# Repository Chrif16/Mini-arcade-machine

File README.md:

# Mini-arcade-machine
a small nes emulation console in the shape of an arcade machine. containing an esp32 s3 and a 2.8 inch tft screen.
this is a part of hackclub's half life event.

# Wiring
the micro controller used is an esp32 s3  because it has more computing power, the display is a standart 2.8 inch display, the controller is a joy stick plus 4 buttons for A,B,START and SELECT.i also used an audio amplifier and hooked it up to an 8ohm speaker. and also a micro sd card reader to read your game roms. 

# pcb
i put all the buttons and controls on the same pcb so that the wiring and mounting is a little bit easier

# 3D model
it has screw holes for mounting everything that has monting holes and the rest have stands that fix the part in place

# firmware
i used the anemoia esp32 nes emulator firmware and reconfigured it to work with my wiring and joystick support
thank you to the anemoia team for making my life easier and making this project possible.
# How to build
for screws and such it is recommended you find them localy for cheap. First, you should screw in place the components with screw holes, and then flash you esp32 s3, and after that youshould slide the speaker in place and plug in place the esp32 and the pam8043 amplifier. and finally solder wire between everything and close the lid and you've got yourself your very own arcade machine
# How to flash
Download and install the Arduino IDE.
In File → Preferences → Additional boards manager URLs , add:
https://espressif.github.io/arduino-esp32/package_esp32_index.json
Download the ESP32 board support v3.2.1 through Tools → Board → Boards Manager .
Important:Make sure to download version 3.2.1, as different board versions may have worse performance.
Navigate to your Arduino Libraries folder: (Default location): Documents/Arduino/libraries/TFT_eSPI
Copy your desired User_Setup.h file in the /User_Setups folder from this repository into TFT_eSPI/ and overwrite the file. Optionally, edit the #define pins as desired.
Download the SdFat and TFT_eSPI libraries from Tools → Manage Libraries .
Locate your ESP32 Arduino platform directory. This is typically at:
\Users\{username}\AppData\Local\Arduino15\packages\esp32\hardware\esp32\{version}\
Copy the platform.txt file from this repository and paste into that folder. This file defines additional compiler flags and optimizations used by Anemoia-ESP32.
Connect your ESP32 via USB.
In the Arduino IDE, go to Tools → Board and select your ESP32 s3 board .
Click Upload or press Ctrl+U to build and flash the emulator.
# BOM
|number of parts|part                      |link                                                                                                                                                                                                                                                                                                                                                                                                                                                                                                                                                                                                                                                                                                                                                                                                                                                                                                                                       |price |
|---------------|--------------------------|-------------------------------------------------------------------------------------------------------------------------------------------------------------------------------------------------------------------------------------------------------------------------------------------------------------------------------------------------------------------------------------------------------------------------------------------------------------------------------------------------------------------------------------------------------------------------------------------------------------------------------------------------------------------------------------------------------------------------------------------------------------------------------------------------------------------------------------------------------------------------------------------------------------------------------------------|------|
|1              |esp32 s3                  |https://ar.aliexpress.com/item/1005012593038007.html?spm=a2g0o.productlist.main.3.56fbd68dsFV1H7&algo_pvid=a583c642-2f95-4179-8c1e-22964e750e76&algo_exp_id=a583c642-2f95-4179-8c1e-22964e750e76-51&pdp_ext_f=%7B%22order%22%3A%2220%22%2C%22eval%22%3A%221%22%2C%22fromPage%22%3A%22search%22%7D&pdp_npi=6%40dis%21USD%213.30%212.04%21%21%213.30%212.04%21%40212a6e3217932889916021693e2399%2112000059750848637%21sea%21TN%210%21ABX%211%210%21n_tag%3A-29910%3Bd%3Aa568ec5c%3Bm03_new_user%3A-29895%3BpisId%3A5000000219357547&curPageLogUid=UTveZqjZShm2&utparam-url=scene%3Asearch%7Cquery_from%3A%7Cx_object_id%3A1005012593038007%7C_p_origin_prod%3A                                                                                                                                                                                                                                                                               |$3.3  |
|1              |joystick                  |https://ar.aliexpress.com/item/1005007846718456.html?spm=a2g0o.detail.pcDetailBottomMoreOtherSeller.2.21f2pCFkpCFkvH&gps-id=pcDetailBottomMoreOtherSeller&scm=1007.40050.354490.0&scm_id=1007.40050.354490.0&scm-url=1007.40050.354490.0&pvid=c3bb454c-9df1-4c85-98ab-45f0fbe84c14&_t=gps-id%3ApcDetailBottomMoreOtherSeller%2Cscm-url%3A1007.40050.354490.0%2Cpvid%3Ac3bb454c-9df1-4c85-98ab-45f0fbe84c14%2Ctpp_buckets%3A668%232846%238112%231997&pdp_ext_f=%7B%22order%22%3A%22173%22%2C%22eval%22%3A%221%22%2C%22sceneId%22%3A%2230050%22%2C%22fromPage%22%3A%22recommend%22%7D&pdp_npi=6%40dis%21USD%215.16%214.12%21%21%2134.22%2127.35%21%400b15841617932898666012194e106e%2112000042509532021%21rec%21TN%21%21ABX%211%210%21n_tag%3A-29910%3Bd%3Aa568ec5c%3Bm03_new_user%3A-29895%3BpisId%3A5000000219357547&utparam-url=scene%3ApcDetailBottomMoreOtherSeller%7Cquery_from%3A%7Cx_object_id%3A1005007846718456%7C_p_origin_prod%3A|$5.17 |
|4              |tactile switch            |https://ar.aliexpress.com/item/1005011812626568.html?spm=a2g0o.productlist.main.23.6f5310e12pQhW4&algo_pvid=3927fdfa-c4f7-4eb8-8cac-7451e68c7490&algo_exp_id=3927fdfa-c4f7-4eb8-8cac-7451e68c7490-20&pdp_ext_f=%7B%22order%22%3A%2232%22%2C%22eval%22%3A%221%22%2C%22fromPage%22%3A%22search%22%7D&pdp_npi=6%40dis%21USD%211.83%211.55%21%21%2112.12%2110.29%21%402101528c17935770888642543e1188%2112000056679091154%21sea%21TN%210%21ABX%211%210%21n_tag%3A-29910%3Bd%3Aa568ec5c%3Bm03_new_user%3A-29895%3BpisId%3A5000000220711916&curPageLogUid=4TdwuWLgh8Dj&utparam-url=scene%3Asearch%7Cquery_from%3A%7Cx_object_id%3A1005011812626568%7C_p_origin_prod%3A                                                                                                                                                                                                                                                                            |$1.86 |
|1              |2.8 inch tft display      |https://ar.aliexpress.com/item/1005003200362110.html?spm=a2g0o.productlist.main.2.3600224f0En55j&algo_pvid=167a9fb6-b7e5-4707-ab2f-96c15c30cfc4&algo_exp_id=167a9fb6-b7e5-4707-ab2f-96c15c30cfc4-5&pdp_ext_f=%7B%22order%22%3A%22756%22%2C%22eval%22%3A%221%22%2C%22fromPage%22%3A%22search%22%7D&pdp_npi=6%40dis%21USD%211.17%211.08%21%21%211.17%211.08%21%402140ebf317932901873541384e0f97%2112000043066579396%21sea%21TN%210%21ABX%211%210%21n_tag%3A-29910%3Bd%3Aa568ec5c%3Bm03_new_user%3A-29895&curPageLogUid=4rq1L7QYxhW6&utparam-url=scene%3Asearch%7Cquery_from%3A%7Cx_object_id%3A1005003200362110%7C_p_origin_prod%3A                                                                                                                                                                                                                                                                                                          |$3.75 |
|1              |8ohm speaker              |https://ar.aliexpress.com/item/1005008222538249.html?spm=a2g0o.productlist.main.1.62454b4a0v584Y&algo_pvid=6c74a62d-0b34-48e1-af19-f2736b5fe1ce&algo_exp_id=6c74a62d-0b34-48e1-af19-f2736b5fe1ce-22&pdp_ext_f=%7B%22order%22%3A%22112%22%2C%22eval%22%3A%221%22%2C%22fromPage%22%3A%22search%22%7D&pdp_npi=6%40dis%21USD%211.55%210.79%21%21%2110.25%215.23%21%402140c7a717934848068521191e0ead%2112000044284454693%21sea%21TN%210%21ABX%211%210%21n_tag%3A-29910%3Bd%3Aa568ec5c%3Bm03_new_user%3A-29895&curPageLogUid=XcFHx8rxMi0L&utparam-url=scene%3Asearch%7Cquery_from%3A%7Cx_object_id%3A1005008222538249%7C_p_origin_prod%3A                                                                                                                                                                                                                                                                                                        |$1.55 |
|1              |pam8403                   |https://ar.aliexpress.com/item/1005008969108597.html?spm=a2g0o.productlist.main.1.17ca3525dF6qvr&algo_pvid=c47db981-9a39-408b-9cee-1de599908a30&algo_exp_id=c47db981-9a39-408b-9cee-1de599908a30-22&pdp_ext_f=%7B%22order%22%3A%22878%22%2C%22eval%22%3A%221%22%2C%22fromPage%22%3A%22search%22%7D&pdp_npi=6%40dis%21USD%210.11%210.09%21%21%210.71%210.58%21%400be7129d17932900547541027e0e98%2112000047407916044%21sea%21TN%210%21ABX%211%210%21n_tag%3A-29910%3Bd%3Aa568ec5c%3Bm03_new_user%3A-29895&curPageLogUid=2t0GGXKwKDnm&utparam-url=scene%3Asearch%7Cquery_from%3A%7Cx_object_id%3A1005008969108597%7C_p_origin_prod%3A                                                                                                                                                                                                                                                                                                         |$0.52 |
|1              |microsd card reader module|https://ar.aliexpress.com/item/1005013449177070.html?spm=a2g0o.productlist.main.3.4a206e32aK9FhL&algo_pvid=c688316a-47dc-4648-969d-7a7321d2d872&algo_exp_id=c688316a-47dc-4648-969d-7a7321d2d872-3&pdp_ext_f=%7B%22order%22%3A%221%22%2C%22eval%22%3A%221%22%2C%22fromPage%22%3A%22search%22%7D&pdp_npi=6%40dis%21USD%213.92%213.33%21%21%2126.00%2122.10%21%402141147417932880151682451e0ec3%2112000061211584902%21sea%21TN%210%21ABX%211%210%21n_tag%3A-29910%3Bd%3Aa568ec5c%3Bm03_new_user%3A-29895%3BpisId%3A5000000220779582&curPageLogUid=uHO7fR8zfuxp&utparam-url=scene%3Asearch%7Cquery_from%3A%7Cx_object_id%3A1005013449177070%7C_p_origin_prod%3A                                                                                                                                                                                                                                                                               |$0.76 |
|5              |pcb                       |jlcpcb                                                                                                                                                                                                                                                                                                                                                                                                                                                                                                                                                                                                                                                                                                                                                                                                                                                                                                                                     |$4    |
|1              |3d printing               |jlcp                                                                                                                                                                                                                                                                                                                                                                                                                                                                                                                                                                                                                                                                                                                                                                                                                                                                                                                                       |$11.41|
|               |total                     |                                                                                                                                                                                                                                                                                                                                                                                                                                                                                                                                                                                                                                                                                                                                                                                                                                                                                                                                           |$32.32|

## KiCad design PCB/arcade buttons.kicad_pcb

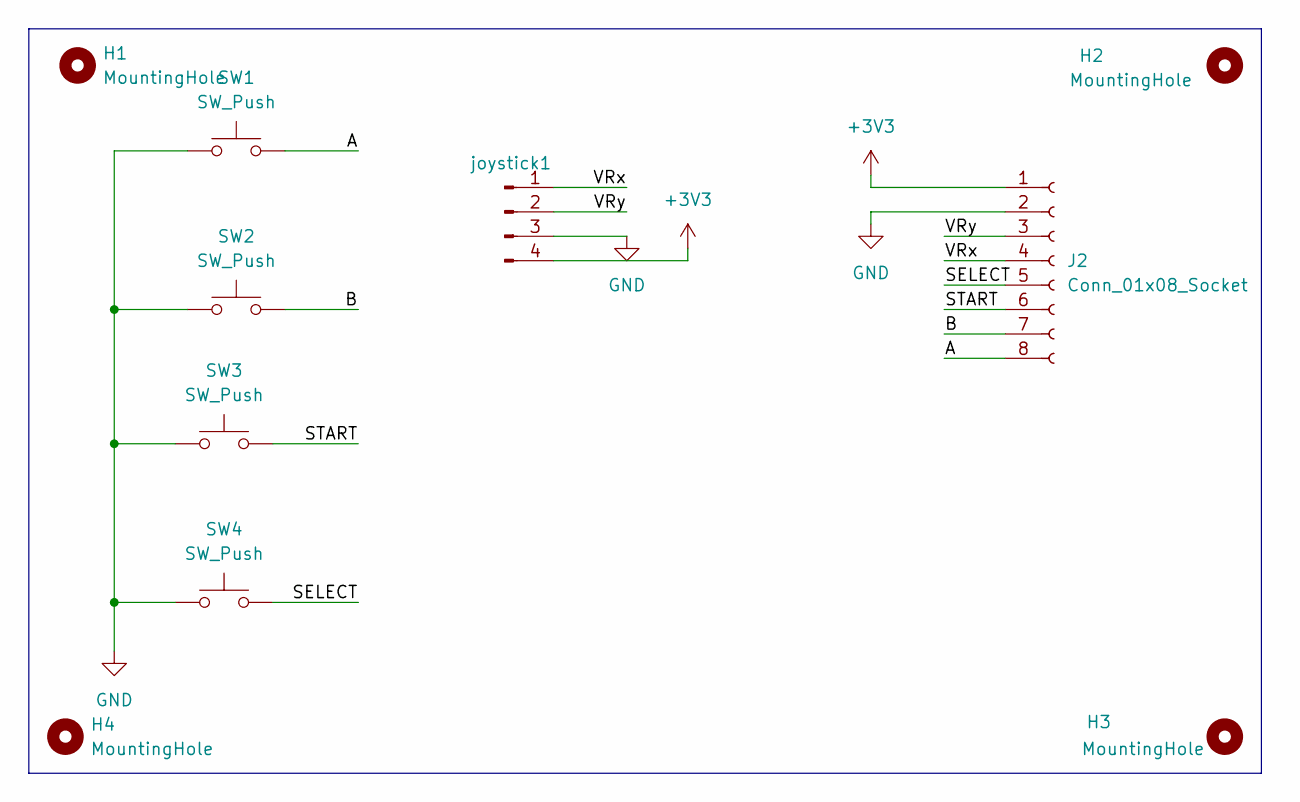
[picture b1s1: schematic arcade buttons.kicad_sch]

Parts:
H1, H2, H3, H4: MountingHole; MountingHole_2.5mm
J2: Conn_01x08_Socket; PinHeader_1x08_P2.54mm_Vertical
SW1, SW2, SW3, SW4: SW_Push; SW_PUSH_6mm
joystick1: Conn_01x04_Pin; PinHeader_1x04_P2.54mm_Vertical

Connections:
+3V3: J2.1, joystick1.4
/A: J2.8, SW1.2
/B: J2.7, SW2.2
/SELECT: J2.5, SW4.2
/START: J2.6, SW3.2
/VRx: J2.4, joystick1.1
/VRy: J2.3, joystick1.2
GND: J2.2, SW1.1, SW2.1, SW3.1, SW4.1, joystick1.3

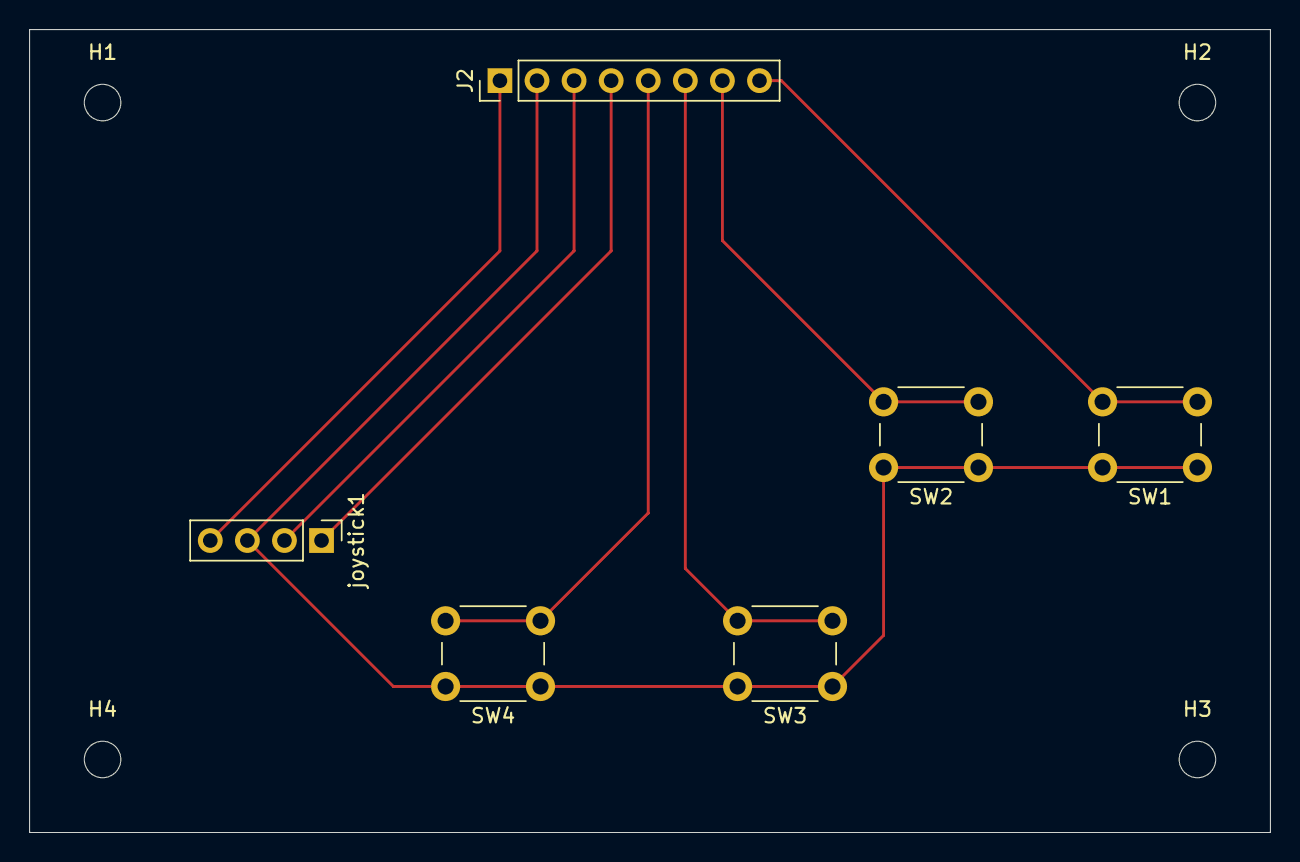
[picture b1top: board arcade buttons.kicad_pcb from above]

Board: 2 copper layers, 85.0 x 55.0 mm, 10 parts (0 on the bottom side), 8 nets.
